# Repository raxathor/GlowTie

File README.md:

# Glowtie
## The light-up bowtie you control over Wifi!

This project/repository is inspired by Stephen Hawes.
https://www.youtube.com/@stephen_hawes
https://github.com/sphawes/glowtie
https://stephenhawes.com/glowtie/

Welcome to the source for the [Glowtie](http://glowtie.io)! The Glowtie is a light-up bowtie you control over Wifi. The onboard ESP8266 puts out an access point network you can connect to with your phone. Navigate to 192.168.4.1 in your browser and you'll find the Glowtie control page, where you can change the colors and the patterns of the lights.

This Github repository holds all the information needed to create a bowtie, from 3D models to schematics. This page will be helpful if you're looking to recreate the glowtie, or hack it!

For more information about the Glowtie, check out Glowtie.io.

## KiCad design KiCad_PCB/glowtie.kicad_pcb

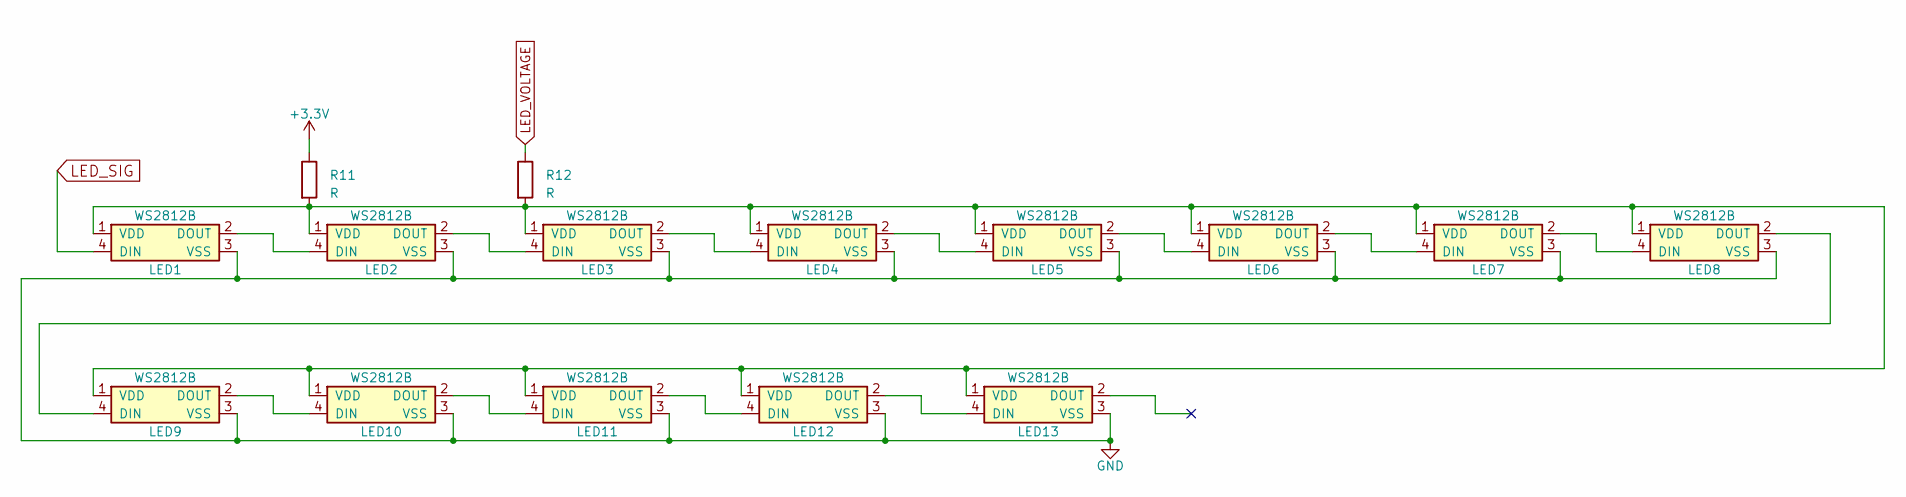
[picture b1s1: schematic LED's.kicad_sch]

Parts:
LED1, LED2, LED3, LED4, LED5, LED6, LED7, LED8, LED9, LED10, LED11, LED12, LED13: WS2812B
R11, R12: R; R_0603_1608Metric

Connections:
+3V3: R11.1; also elsewhere on the board
GND: LED1.3 (VSS), LED2.3 (VSS), LED3.3 (VSS), LED4.3 (VSS), LED5.3 (VSS), LED6.3 (VSS), LED7.3 (VSS), LED8.3 (VSS), LED9.3 (VSS), LED10.3 (VSS), LED11.3 (VSS), LED12.3 (VSS), LED13.3 (VSS); also elsewhere on the board
LED_SIG: LED1.4 (DIN); also elsewhere on the board
LED_VOLTAGE: R12.1; also elsewhere on the board
unnamed: LED1.2 (DOUT), LED2.4 (DIN)
unnamed: LED1.1 (VDD), LED2.1 (VDD), LED3.1 (VDD), LED4.1 (VDD), LED5.1 (VDD), LED6.1 (VDD), LED7.1 (VDD), LED8.1 (VDD), LED9.1 (VDD), LED10.1 (VDD), LED11.1 (VDD), LED12.1 (VDD), LED13.1 (VDD), R11.2, R12.2
unnamed: LED2.2 (DOUT), LED3.4 (DIN)
unnamed: LED3.2 (DOUT), LED4.4 (DIN)
unnamed: LED4.2 (DOUT), LED5.4 (DIN)
unnamed: LED5.2 (DOUT), LED6.4 (DIN)
unnamed: LED6.2 (DOUT), LED7.4 (DIN)
unnamed: LED7.2 (DOUT), LED8.4 (DIN)
unnamed: LED8.2 (DOUT), LED9.4 (DIN)
unnamed: LED9.2 (DOUT), LED10.4 (DIN)
unnamed: LED10.2 (DOUT), LED11.4 (DIN)
unnamed: LED11.2 (DOUT), LED12.4 (DIN)
unnamed: LED12.2 (DOUT), LED13.4 (DIN)

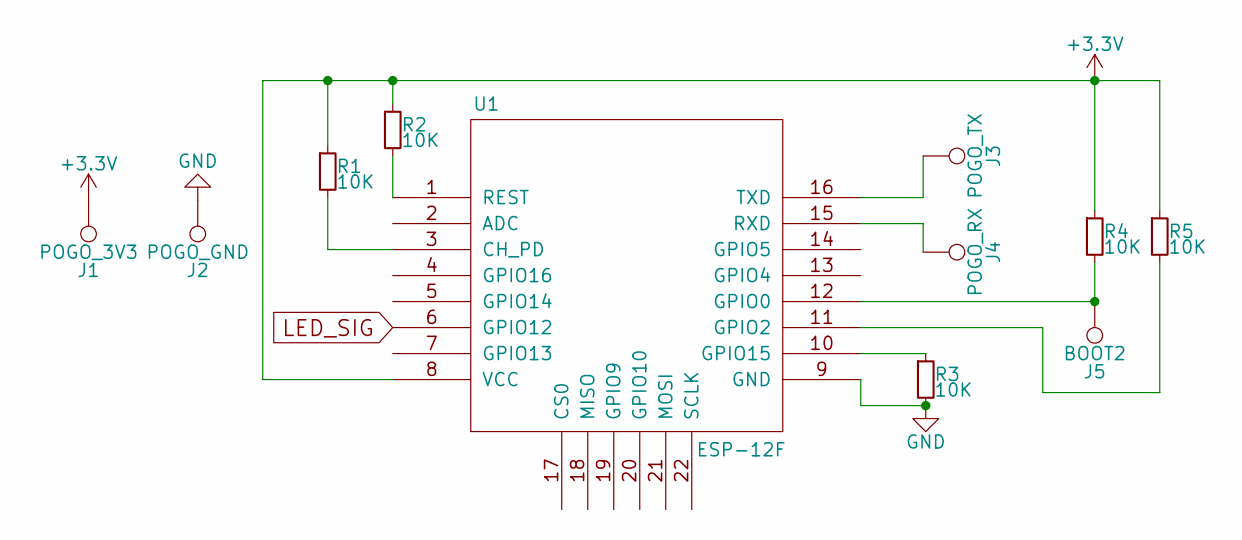
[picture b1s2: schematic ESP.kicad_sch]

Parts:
J1: POGO_3V3; TestPoint_Pad_D1.5mm
J2: POGO_GND; TestPoint_Pad_D1.5mm
J3: POGO_TX; TestPoint_Pad_D1.5mm
J4: POGO_RX; TestPoint_Pad_D1.5mm
J5: BOOT2; TestPoint_Pad_D1.5mm
R1, R2, R3, R4, R5: 10K; R_0805_2012Metric_Pad1.20x1.40mm_HandSolder
U1: ESP-12F; ESP-12E_SMD

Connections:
+3V3: J1.1, R1.1, R2.1, R4.1, R5.1, U1.8 (VCC); also elsewhere on the board
GND: J2.1, R3.2, U1.9 (GND); also elsewhere on the board
LED_SIG: U1.6 (GPIO12); also elsewhere on the board
unnamed: R1.2, U1.3 (CH_PD)
unnamed: J5.1, R4.2, U1.12 (GPIO0)
unnamed: R5.2, U1.11 (GPIO2)
unnamed: R3.1, U1.10 (GPIO15)
unnamed: R2.2, U1.1 (REST)
unnamed: J4.1, U1.15 (RXD)
unnamed: J3.1, U1.16 (TXD)

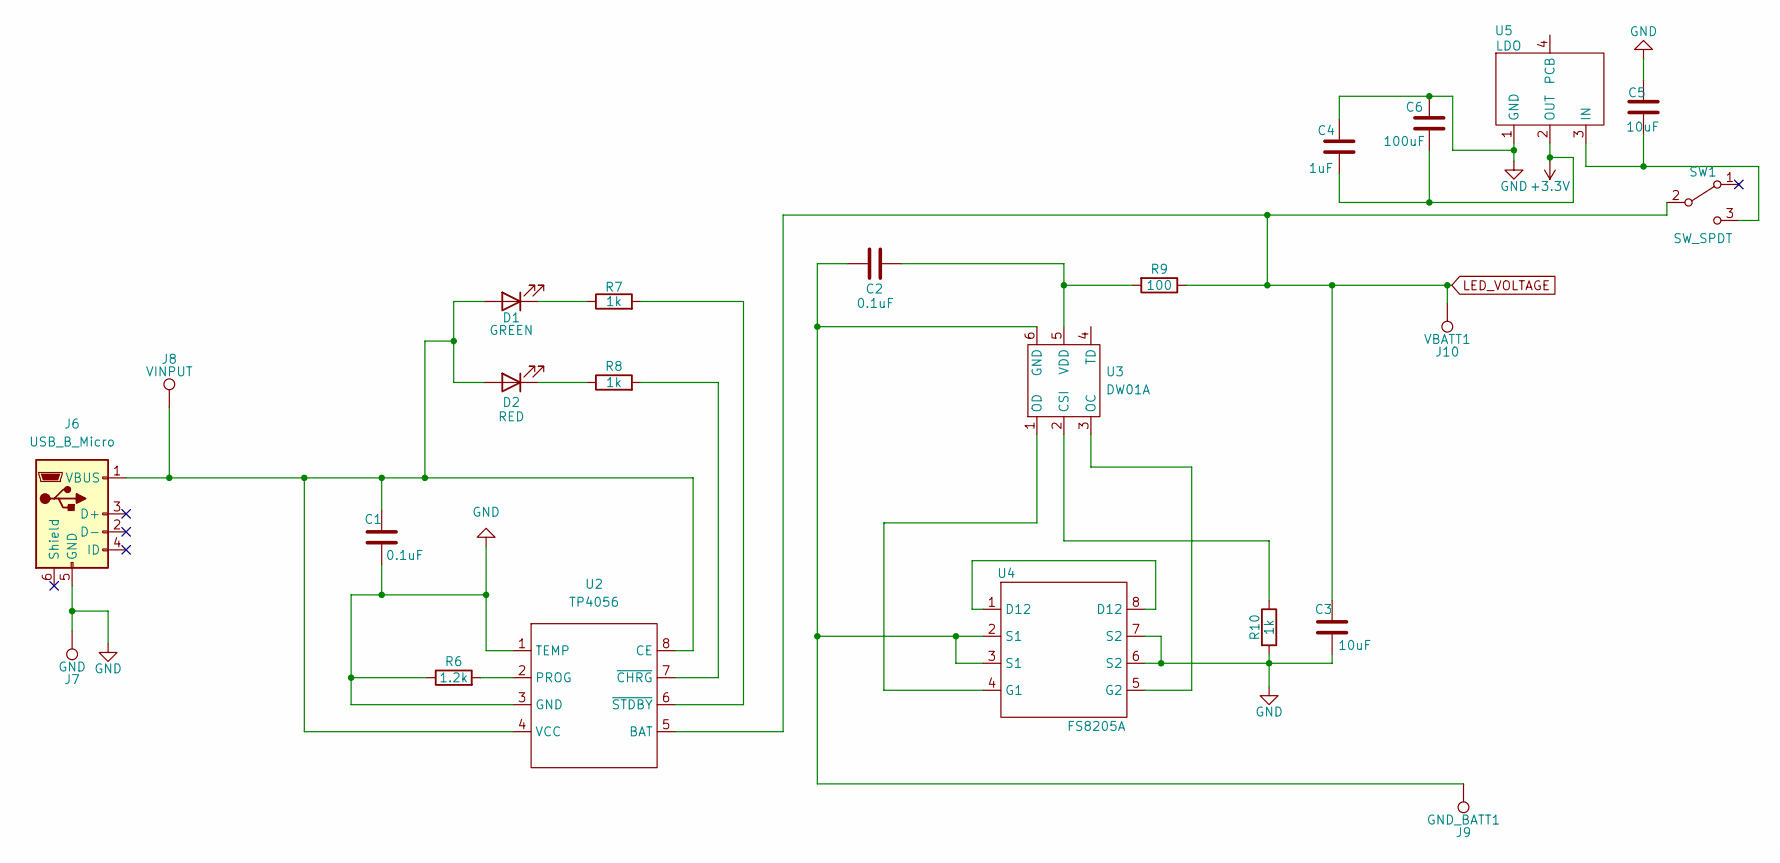
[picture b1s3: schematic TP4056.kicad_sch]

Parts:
C1, C2: 0.1uF; C_0805_2012Metric_Pad1.18x1.45mm_HandSolder
C3: 10uF; C_0805_2012Metric_Pad1.18x1.45mm_HandSolder
C4: 1uF; C_0805_2012Metric_Pad1.18x1.45mm_HandSolder
C5: 10uF; Tantalum_10uF
C6: 100uF; Tantalum_100uF
D1: GREEN; LED_0805_2012Metric_Pad1.15x1.40mm_HandSolder
D2: RED; LED_0805_2012Metric_Pad1.15x1.40mm_HandSolder
J6: USB_B_Micro; USB_Micro-B_Molex-105017-0001
J7: GND; TestPoint_Pad_D1.5mm
J8: VINPUT; TestPoint_Pad_D1.5mm
J9: GND_BATT1; TestPoint_Pad_D1.5mm
J10: VBATT1; TestPoint_Pad_D1.5mm
R6: 1.2k; R_0805_2012Metric_Pad1.20x1.40mm_HandSolder
R7, R8, R10: 1k; R_0805_2012Metric_Pad1.20x1.40mm_HandSolder
R9: 100; R_0805_2012Metric_Pad1.20x1.40mm_HandSolder
SW1: SW_SPDT; MSK12C02
U2: TP4056
U3: DW01A
U4: FS8205A
U5: LDO; AMS1117-3.3

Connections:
+3V3: C4.1, C6.1, U5.2 (OUT); also elsewhere on the board
GND: C1.2, C3.2, C4.2, C5.1, C6.2, J6.5 (GND), J7.1, R6.1, R10.2, U2.1 (TEMP), U2.3 (GND), U4.6 (S2), U4.7 (S2), U5.1 (GND); also elsewhere on the board
LED_VOLTAGE: C3.1, J10.1, R9.1, SW1.2 (B), U2.5 (BAT); also elsewhere on the board
unnamed: C1.1, D1.2 (A), D2.2 (A), J6.1 (VBUS), J8.1, U2.4 (VCC), U2.8 (CE)
unnamed: D1.1 (K), R7.1
unnamed: D2.1 (K), R8.1
unnamed: C5.2, SW1.3 (C), U5.3 (IN)
unnamed: R6.2, U2.2 (PROG)
unnamed: R8.2, U2.7 (~CHRG)
unnamed: R7.2, U2.6 (~STDBY)
unnamed: R10.1, U3.2 (CSI)
unnamed: C2.1, J9.1, U3.6 (GND), U4.2 (S1), U4.3 (S1)
unnamed: U3.3 (OC), U4.5 (G2)
unnamed: U3.1 (OD), U4.4 (G1)
unnamed: C2.2, R9.2, U3.5 (VDD)
unnamed: U4.1 (D12), U4.8 (D12)

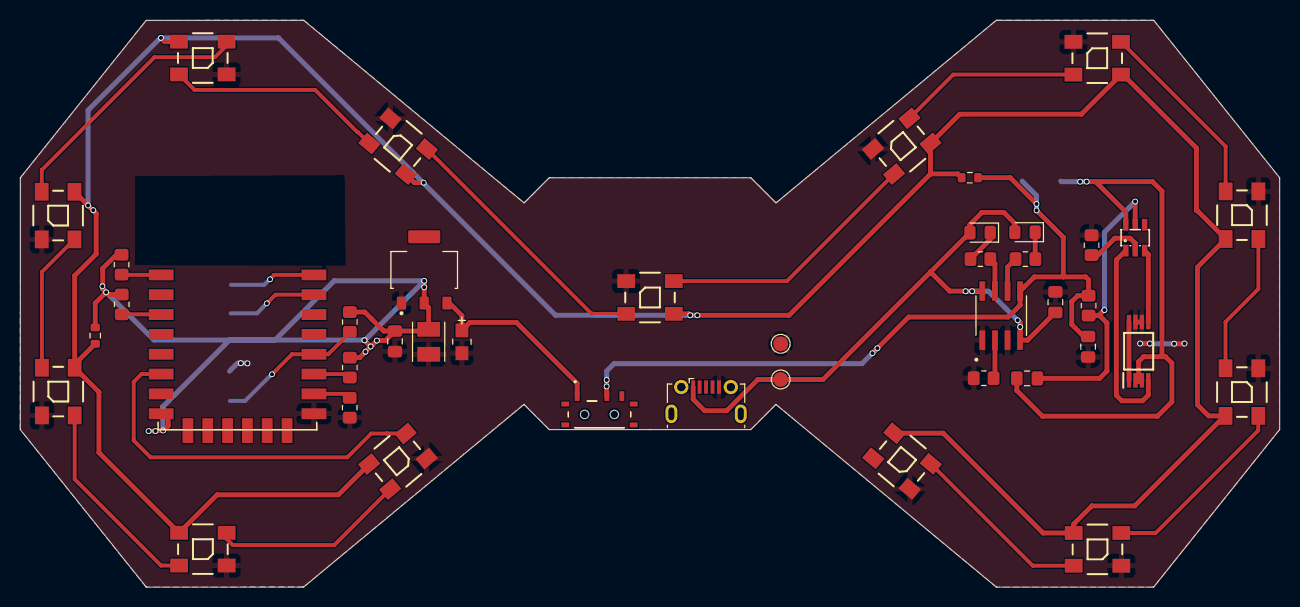
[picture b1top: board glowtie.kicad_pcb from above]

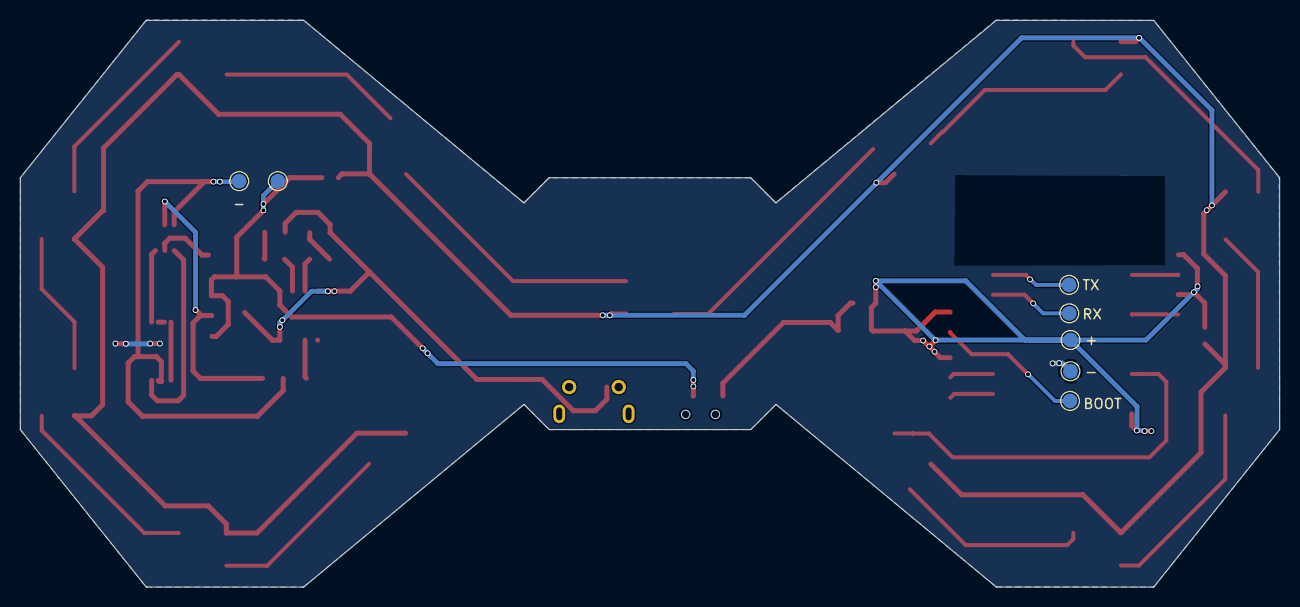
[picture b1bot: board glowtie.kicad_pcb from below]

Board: 2 copper layers, 127.0 x 57.2 mm, 49 parts (7 on the bottom side), 37 nets.

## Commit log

2023-09-09 changes/attributions
